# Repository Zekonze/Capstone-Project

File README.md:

# Capstone-Project
This project utilizes an ESP32 microcontroller and an MQ-2 gas sensor to create a precision LPG leak detection system that translates raw analog sensor voltage into accurate (PPM) software maintains high accuracy, allowing you to implement a custom safety threshold of 3000 PPM that reliably distinguishes between minor background gas interference 

Here are the Parts!

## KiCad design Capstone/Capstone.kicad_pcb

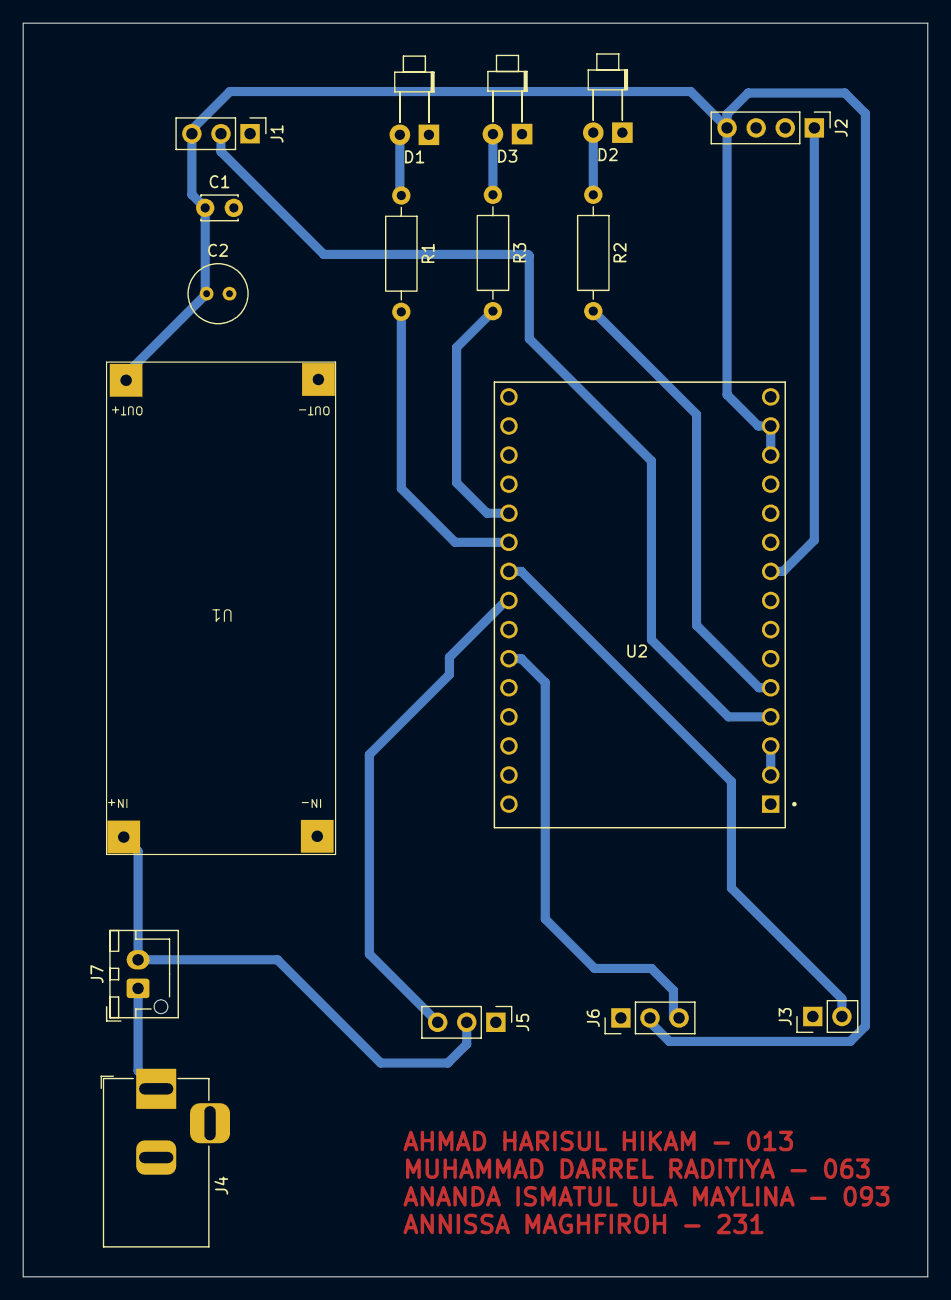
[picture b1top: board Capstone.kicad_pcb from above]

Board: 2 copper layers, 79.0 x 109.5 mm, 17 parts (0 on the bottom side), 16 nets.

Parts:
C1: C; C_Disc_D3.0mm_W2.0mm_P2.50mm
C2: C_Polarized; C_Radial_D5.0mm_H5.0mm_P2.00mm
D1: LED_red; LED_D1.8mm_W1.8mm_H2.4mm_Horizontal_O3.81mm_Z1.6mm
D2: LED_green; LED_D1.8mm_W1.8mm_H2.4mm_Horizontal_O3.81mm_Z1.6mm
D3: LED_yellow; LED_D1.8mm_W1.8mm_H2.4mm_Horizontal_O3.81mm_Z1.6mm
J1: PIR; PinHeader_1x03_P2.54mm_Vertical
J2: MQ2; PinHeader_1x04_P2.54mm_Vertical
J3: Buzzer; PinHeader_1x02_P2.54mm_Vertical
J4: Barrel_Jack_Switch; BarrelJack_Horizontal
J5: servo12V; PinHeader_1x03_P2.54mm_Vertical
J6: servo5V; PinHeader_1x03_P2.54mm_Vertical
J7: Screw_Terminal_01x02; JST_XH_B2B-XH-AM_1x02_P2.50mm_Vertical
R1, R2, R3: 1k; R_Axial_DIN0207_L6.3mm_D2.5mm_P10.16mm_Horizontal
U1: LM2596HVS Module; LM2596
U2: ESP32-C3-DEVKITM-1; XCVR_ESP32-C3-DEVKITM-1

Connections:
3V3: U2.2 (3V3), U2.3 (3V3)
5V: C1.1, C2.1, J1.3, J2.4, J6.2, U1.3 (OUT+), U2.13 (5V), U2.14 (5V)
GND: C1.2, C2.2, D1.1 (K), D2.1 (K), D3.1 (K), J1.1, J2.3, J3.1, J4.2, J5.1, J6.1, U1.2 (IN-), U1.4 (OUT-), U2.1 (GND), U2.6 (GND), U2.8 (GND), U2.12 (GND), U2.15 (GND), U2.16 (GND), U2.19 (GND), U2.24 (GND), U2.27 (GND), U2.30 (GND)
unnamed: D1.2 (A), R1.1
unnamed: D2.2 (A), R2.1
unnamed: D3.2 (A), R3.1
unnamed: J1.2, U2.4 (IO2)
unnamed: J2.1, U2.9 (IO0)
unnamed: J3.2, U2.22 (IO6)
unnamed: J5.2, J7.2, U1.1 (IN+)
unnamed: J5.3, U2.23 (IO7)
unnamed: J6.3, U2.25 (IO8)
unnamed: J4.1, J7.1
unnamed: R2.2, U2.5 (IO3)
unnamed: R3.2, U2.20 (IO4)
unnamed: R1.2, U2.21 (IO5)

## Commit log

2026-05-29 add pembacaan gas disini
2026-05-29 INTEGRASI
    Integrasi Sensor PIR dan MQ2 ke buzzer dan LED melalui gerbang AND
2026-06-17 Create Integrasi_Sensor_Buzzer_Servo
2026-06-17 Update README with image and parts section
    Added an image and a section for parts in the README.
